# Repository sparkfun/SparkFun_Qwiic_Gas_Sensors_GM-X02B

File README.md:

-----------------------------------------------------------------------

The SparkFun Gas Sensor - GM-XX2B (Qwiic) are a series of nine compact gas-sensing breakouts built around the GM-XX2B series of gas sensors from Winsen. The GM-XX2B sensors are metal-oxide semiconductor (MOS) sensors that measures the specified gas (or gases), and its analog output rises with gas concentration. To make it Qwiic-friendly, we fed that analog signal into an onboard 10-bit I2C ADC, so you can read gas levels straight over I2C with no external ADC required. The boards includes a pair of Qwiic connectors as well as a PTH header that breaks out the raw analog VOUT alongside SDA and SCL for non-Qwiic setups.

This series includes Qwiic breakouts for the [GM-102B Nitrogen Dioxide Gas Sensor](https://www.sparkfun.com/sparkfun-nitrogen-dioxide-gas-sensor-gm-102b-qwiic.html), [GM-202B Ethanol & Smoke Gas Sensor](https://www.sparkfun.com/sparkfun-ethanol-smoke-gas-sensor-gm-202b-qwiic.html), [GM-302B Alcohol/Ethanol Gas Sensor](https://www.sparkfun.com/sparkfun-alcohol-ethanol-gas-sensor-gm-302b-qwiic.html), [GM-402B Combustible Gas Sensor](https://www.sparkfun.com/sparkfun-combustible-gas-sensor-gm-402b-qwiic.html), [GM-502B VOC Gas Sensor](https://www.sparkfun.com/sparkfun-voc-gas-sensor-gm-502b-qwiic.html), [GM-512B Bad Breath Gas Sensor](https://www.sparkfun.com/sparkfun-bad-breath-gas-sensor-gm-512b-qwiic.html), [GM-602B Hydrogen Sulfide Gas Sensor](https://www.sparkfun.com/sparkfun-hydrogen-sulfide-gas-sensor-gm-602b-qwiic.html), [GM-702B Carbon Monoxide Gas Sensor](https://www.sparkfun.com/sparkfun-carbon-monoxide-gas-sensor-gm-702b-qwiic.html) and [GM-802B Ammonia Gas Sensor](https://www.sparkfun.com/sparkfun-ammonia-gas-sensor-gm-802b-qwiic.html).

**Note:** Out of the box the GM-XX2B sensors are great for relative measurement and threshold alerts. Absolute ppm readings require calibration, and the sensor must be preheated before first use. See the Hookup Guide for details.

## Repository Contents

* **/docs** - Documentation files for GitHub pages
* **/Documents** - Datasheets, additional product information
* **/Hardware** - KiCad design files (.kicad_sch, .kicad_pcb)
* **/Production** - Production panel files

## Documentation

* **[Library](https://github.com/sparkfun/SparkFun_GM-X02B_Arduino_Library)** - Arduino library for the SparkFun Qwiic MEMS Hydrogen Sulfide Sensor - GM-602B.
* **[Hookup Guide](https://docs.sparkfun.com/SparkFun_Qwiic_MEMS_Hydrogen_Sulfide_Sensor_GM-602B/)** - Basic hookup guide for the SparkFun Qwiic MEMS Hydrogen Sulfide Sensor - GM-602B, including preheating, calibration, and handling cautions.

## Product Versions

* **[SEN-32064](https://www.sparkfun.com/sparkfun-nitrogen-dioxide-gas-sensor-gm-102b-qwiic.html)** - Initial release of the SparkFun Nitrogen Dioxide Gas Sensor - GM-102B (Qwiic).
* **[SEN-32065](https://www.sparkfun.com/sparkfun-ethanol-smoke-gas-sensor-gm-202b-qwiic.html)** - Initial release of the SparkFun Ethanol & Smoke Gas Sensor - GM-202B (Qwiic).
* **[SEN-32066](https://www.sparkfun.com/sparkfun-alcohol-ethanol-gas-sensor-gm-302b-qwiic.html)** - Initial release of the SparkFun Alcohol/Ethanol Gas Sensor - GM-302B (Qwiic).
* **[SEN-32067](https://www.sparkfun.com/sparkfun-combustible-gas-sensor-gm-402b-qwiic.html)** - Initial release of the SparkFun Combustible Gas Sensor - GM-402B (Qwiic).
* **[SEN-32068](https://www.sparkfun.com/sparkfun-voc-gas-sensor-gm-502b-qwiic.html)** - Initial release of the SparkFun VOC Gas Sensor - GM-502B (Qwiic).
* **[SEN-32069](https://www.sparkfun.com/sparkfun-bad-breath-gas-sensor-gm-512b-qwiic.html)** - Initial release of the SparkFun Bad Breath Gas Sensor - GM-512B (Qwiic).
* **[SEN-31734](https://www.sparkfun.com/sparkfun-hydrogen-sulfide-gas-sensor-gm-602b-qwiic.html)** - Initial release of the SparkFun Bad Breath Gas Sensor - GM-602B (Qwiic).
* **[SEN-32070](https://www.sparkfun.com/sparkfun-carbon-monoxide-gas-sensor-gm-702b-qwiic.html)** - Initial release of the	SparkFun Carbon Monoxide Gas Sensor - GM-702B (Qwiic).
* **[SEN-32071](https://www.sparkfun.com/sparkfun-ammonia-gas-sensor-gm-802b-qwiic.html)** - Initial release of the SparkFun Ammonia Gas Sensor - GM-802B (Qwiic).

## License Information

This product is _**open source**_!

Please review the LICENSE.md file for license information.

If you have any questions or concerns about licensing, please contact technical support on our [SparkFun forums](https://forum.sparkfun.com/viewforum.php?f=152).

Distributed as-is; no warranty is given.

_- Your friends at SparkFun._

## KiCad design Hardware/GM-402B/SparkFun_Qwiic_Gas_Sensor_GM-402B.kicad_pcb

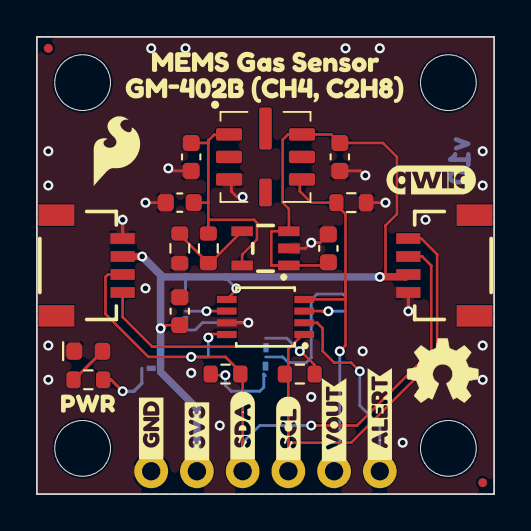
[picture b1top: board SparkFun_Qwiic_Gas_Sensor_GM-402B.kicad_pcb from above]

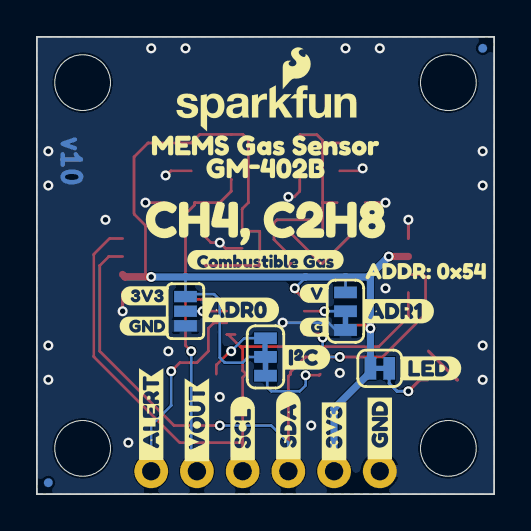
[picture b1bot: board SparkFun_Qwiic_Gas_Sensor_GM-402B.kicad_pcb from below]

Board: 2 copper layers, 25.4 x 25.4 mm, 60 parts (25 on the bottom side), 14 nets.

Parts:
C1, C4, C5: 0.1uF; C_0603_1608Metric
C2, C3: 1.0uF; C_0603_1608Metric
D1: Red; LED_0603_1608Metric_Red
FID1, FID2, FID3, FID4: Fiducial_0.5mm; Fiducial_0.5mm_Mask1mm
G4: OSHW_Logo; Creative_Commons_License
IC2: RT9080N-08GJ5; SOT23-5
IC3: ADC101C021; TSSOP-8_3x3mm_P0.65mm
J1, J2: Qwiic_RA; JST_1x04_P1.0mm_Horizontal_SMD
J3: Conn_01x06; 1x06_P2.54mm
JP1: LED; Jumper_2_NC_Trace
JP2: I²C; Jumper_3_NC-2_Trace
JP3: ADR0; Jumper_3_NO
JP4: ADR1; Jumper_3_NC-1_Trace
R1: 24.9k; R_0603_1608Metric
R2: 10k; R_0603_1608Metric
R3, R6: 4.7k; R_0603_1608Metric
R4, R5: 2.2k; R_0603_1608Metric
Ref**: Val**; OSHW_Logo_4mm
ST1, ST2, ST3, ST4: Standoff
U1: GM-402B; GM-X02
kibuzzard-6A2AF6B9: G***; kibuzzard-6A2AF6B9
kibuzzard-6A2AF6DB: G***; kibuzzard-6A2AF6DB
kibuzzard-6A2AF770: G***; kibuzzard-6A2AF770
kibuzzard-6A2AF782: G***; kibuzzard-6A2AF782
kibuzzard-6A7E2AAD: G***; kibuzzard-6A7E2AAD
kibuzzard-6A15EF4F, kibuzzard-6A15EF4F#2: G***; kibuzzard-6A15EF4F
kibuzzard-6A285C8F: G***; kibuzzard-6A285C8F
kibuzzard-6A285C86: G***; kibuzzard-6A285C86
kibuzzard-6A285C96: G***; kibuzzard-6A285C96
kibuzzard-6A285CA0: G***; kibuzzard-6A285CA0
kibuzzard-6A0365C6: G***; kibuzzard-6A0365C6
kibuzzard-6A6283AE: G***; kibuzzard-6A6283AE
kibuzzard-6A6283BC: G***; kibuzzard-6A6283BC
kibuzzard-6A62839A: G***; kibuzzard-6A62839A
kibuzzard-6A285721: G***; kibuzzard-6A285721
kibuzzard-6A285731: G***; kibuzzard-6A285731
kibuzzard-6A628392: G***; kibuzzard-6A628392
kibuzzard-689A66E2: G***; kibuzzard-689A66E2
kibuzzard-689A66E9: G***; kibuzzard-689A66E9
kibuzzard-689A66EE: G***; kibuzzard-689A66EE
kibuzzard-689A66F4: G***; kibuzzard-689A66F4
kibuzzard-689A642E: G***; kibuzzard-689A642E
kibuzzard-689A6711: G***; kibuzzard-689A6711
kibuzzard-689A6718: G***; kibuzzard-689A6718
kibuzzard-689A6721: G***; kibuzzard-689A6721
kibuzzard-689A6728: G***; kibuzzard-689A6728
kibuzzard-689A6796: G***; kibuzzard-689A6796

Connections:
3.3V: C3.1, C4.1, C5.1, IC2.1 (VIN), IC2.3 (EN), IC3.5 (VA), J1.2, J2.2, J3.2, JP1.2 (B), JP2.2 (B), JP3.1 (A), JP4.3 (C), U1.7 (S+)
ADR0: IC3.3 (ADR0), JP3.2 (B)
ADR1: IC3.6 (ADR1), JP4.2 (B)
ALERT: IC3.2 (ALERT), J3.6
GND: C1.2, C2.2, C3.2, C4.2, C5.2, D1.1 (K), IC2.2 (GND), IC3.7 (GND), J1.1, J2.1, J3.1, JP3.3 (C), JP4.1 (A), R2.1, R6.1, U1.3 (H-)
unnamed: D1.2 (A), R3.1
unnamed: IC2.4 (SNS), R1.1, R2.2
unnamed: JP1.1 (A), R3.2
unnamed: JP2.1 (A), R5.2
unnamed: JP2.3 (C), R4.2
SCL: IC3.1 (SCL), J1.4, J2.4, J3.4, R4.1
SDA: IC3.8 (SDA), J1.3, J2.3, J3.3, R5.1
VH: C1.1, C2.1, IC2.5 (VOUT), R1.2, U1.1 (H+)
VOUT: IC3.4 (VIN), J3.5, R6.2, U1.5 (S-)

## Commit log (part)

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2026-06-01 Moved image to images folder
2026-06-01 Added datasheets and updated I2C Info on schematic
2026-06-09 Updated Datasheets and PCB based on Design Review Feedback
2026-06-09 Edited back silkscreen
2026-06-09 Updated Image
2026-06-11 Implemented Design Review Changes
    - Removed EN
    - Nudged Vias
    - Finalized Silkscreen
    - Updated LDO Symbol
    - Updated Resistor Values
2026-06-12 Updated Sparkle IDs

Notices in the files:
parts and their libraries:
Released under the Creative Commons Attribution Share-Alike 4.0 License
https://creativecommons.org/licenses/by-sa/4.0
